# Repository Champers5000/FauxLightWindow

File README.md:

# FauxLightWindow
Designed to emulate the sun in a windowless space. 
* Uses GPS to determine your location and time in order to calculate luminosity at that location. 
* Electronics implement flickerless dimming of LEDs through a controllable constant current buck converter

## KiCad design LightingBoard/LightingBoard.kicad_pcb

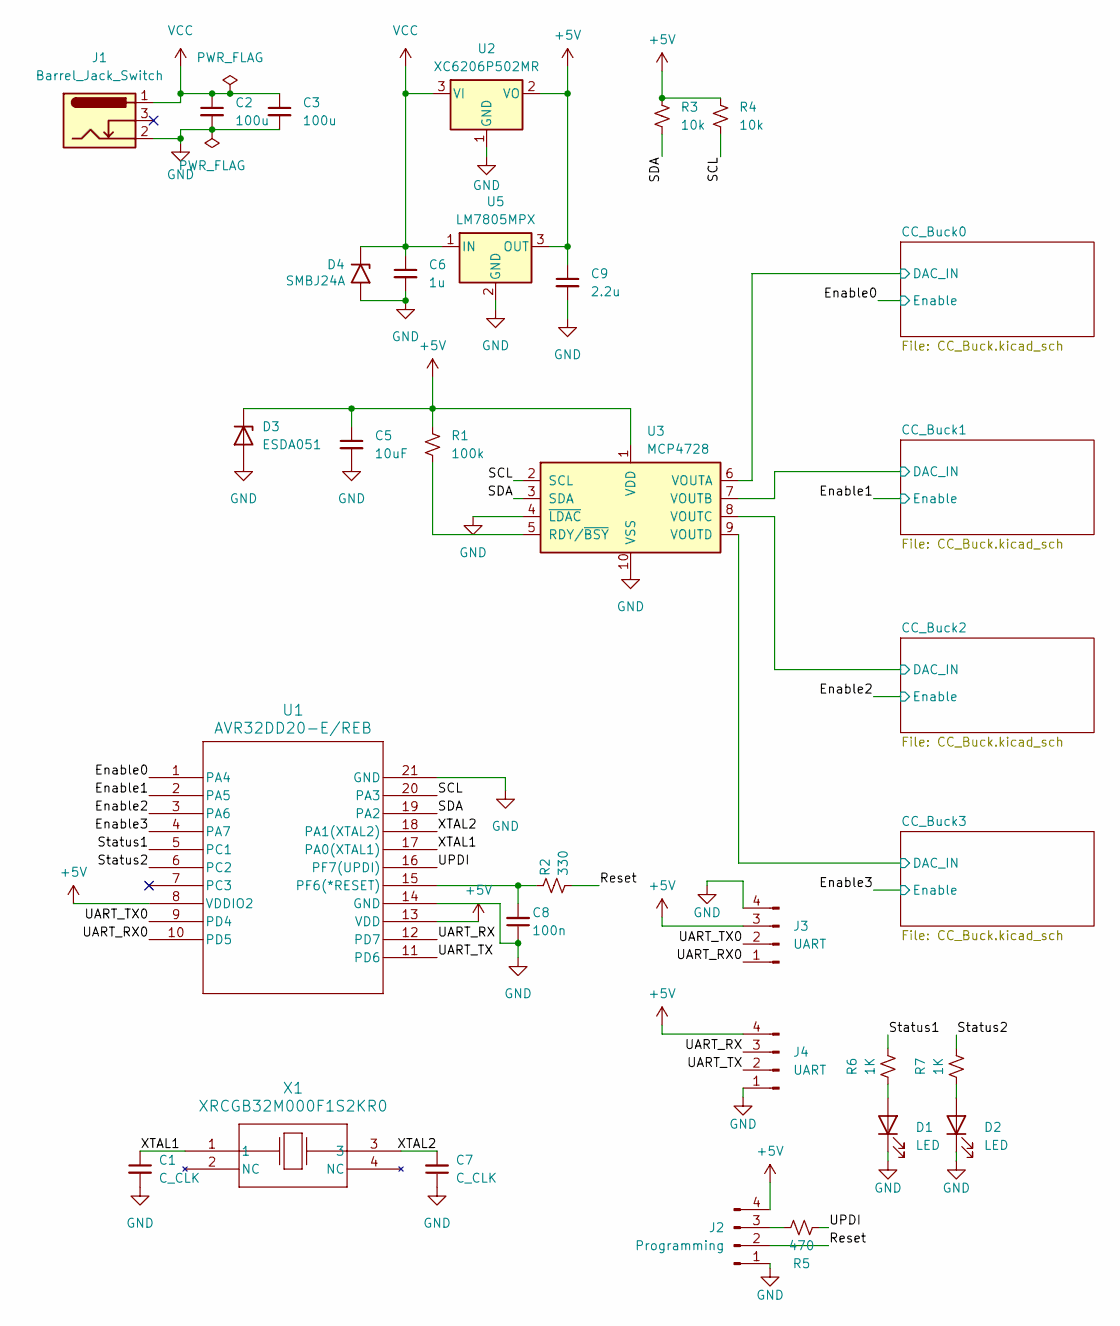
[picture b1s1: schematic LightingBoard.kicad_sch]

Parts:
C1, C7: C_CLK; C_0603_1608Metric
C2, C3: 100u; CP_Elec_6.3x7.7
C5: 10uF; C_0603_1608Metric
C6: 1u; C_0603_1608Metric
C8: 100n; C_0603_1608Metric
C9: 2.2u; C_0603_1608Metric
D1, D2: LED; LED_0805_2012Metric
D3: ESDA051; D_SOD-323
D4: SMBJ24A; D_SMB
J1: Barrel_Jack_Switch; BarrelJack_Horizontal
J2: Programming; PinSocket_1x04_P2.54mm_Vertical
J3: UART; JST_SH_BM04B-SRSS-TB_1x04-1MP_P1.00mm_Vertical
J4: UART; PinSocket_1x04_P2.54mm_Vertical
R1: 100k; R_0603_1608Metric
R2: 330; R_0603_1608Metric
R3, R4: 10k; R_0603_1608Metric
R5: 470; R_0603_1608Metric
R6, R7: 1K; R_0603_1608Metric
U1: AVR32DD20-E/REB; VQFN-20-1EP_3x3mm_P0.4mm_EP1.7x1.7mm
U2: XC6206P502MR; SOT-23
U3: MCP4728; MSOP-10_3x3mm_P0.5mm
U5: LM7805MPX; SOT-223-3_TabPin2
X1: XRCGB32M000F1S2KR0; Crystal_SMD_2016-4Pin_2.0x1.6mm

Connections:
+5V: C5.1, C9.1, D3.1 (K), J2.4, J3.3, J4.4, R1.1, R3.1, R4.1, U1.8 (VDDIO2), U1.13 (VDD), U2.2 (VO), U3.1 (VDD), U5.3 (OUT); also elsewhere on the board
/CC_Buck0/DAC_IN: U3.6 (VOUTA); also elsewhere on the board
/CC_Buck1/DAC_IN: U3.7 (VOUTB); also elsewhere on the board
/CC_Buck2/DAC_IN: U3.8 (VOUTC); also elsewhere on the board
/CC_Buck3/DAC_IN: U3.9 (VOUTD); also elsewhere on the board
/Enable0: U1.1 (PA4); also elsewhere on the board
/Enable1: U1.2 (PA5); also elsewhere on the board
/Enable2: U1.3 (PA6); also elsewhere on the board
/Enable3: U1.4 (PA7); also elsewhere on the board
/Reset: J2.2, R2.1
/SCL: R4.2, U1.20 (PA3), U3.2 (SCL)
/SDA: R3.2, U1.19 (PA2), U3.3 (SDA)
/Status1: R6.2, U1.5 (PC1)
/Status2: R7.2, U1.6 (PC2)
/UART_RX: J4.3, U1.12 (PD7)
/UART_RX0: J3.1, U1.10 (PD5)
/UART_TX: J4.2, U1.11 (PD6)
/UART_TX0: J3.2, U1.9 (PD4)
/UPDI: R5.1, U1.16 (PF7(UPDI))
/XTAL1: C1.1, U1.17 (PA0(XTAL1)), X1.1
/XTAL2: C7.2, U1.18 (PA1(XTAL2)), X1.3
GND: C1.2, C2.2, C3.2, C5.2, C6.2, C7.1, C8.1, C9.2, D1.1 (K), D2.1 (K), D3.2 (A), D4.2 (A2), J1.2, J2.1, J3.4, J4.1, U1.14 (GND), U1.21 (GND), U2.1 (GND), U3.4 (~LDAC), U3.10 (VSS), U5.2 (GND); also elsewhere on the board
unnamed: D1.2 (A), R6.1
unnamed: D2.2 (A), R7.1
unnamed: J2.3, R5.2
unnamed: C8.2, R2.2, U1.15 (PF6(*RESET))
unnamed: R1.2, U3.5 (RDY/~BSY)
VCC: C2.1, C3.1, C6.1, D4.1 (A1), J1.1, U2.3 (VI), U5.1 (IN); also elsewhere on the board

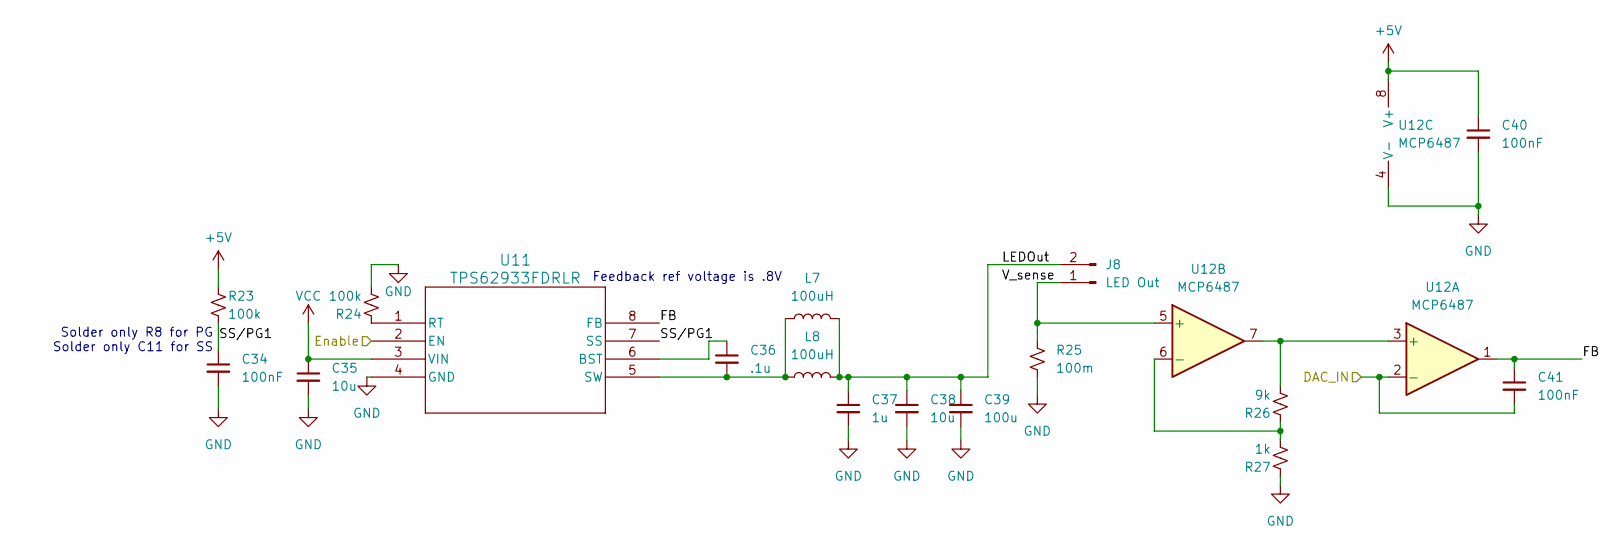
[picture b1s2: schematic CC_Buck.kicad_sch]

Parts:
C34, C40, C41: 100nF; C_0603_1608Metric
C35: 10u; C_0603_1608Metric
C36: .1u; C_0603_1608Metric
C37: 1u; C_0805_2012Metric
C38: 10u; C_0805_2012Metric
C39: 100u; CP_Elec_6.3x7.7
J8: LED Out; PinSocket_1x02_P2.54mm_Vertical
L7: 100uH; 7447231101
L8: 100uH; IND_BOURNS_SDR1307
R23, R24: 100k; R_0603_1608Metric
R25: 100m; R_1206_3216Metric
R26: 9k; R_0603_1608Metric
R27: 1k; R_0603_1608Metric
U11: TPS62933FDRLR; SOT-583-8
U12: MCP6487; MSOP-8_3x3mm_P0.65mm

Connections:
+5V: C40.1, R23.2, U12.8 (V+); also elsewhere on the board
/CC_Buck3/DAC_IN: C41.2, U12.2 (-); also elsewhere on the board
/CC_Buck3/FB: C41.1, U11.8 (FB), U12.1
/CC_Buck3/LEDOut: C37.1, C38.1, C39.1, J8.2, L7.2, L8.2
/CC_Buck3/SS/PG1: C34.1, R23.1, U11.7 (SS)
/CC_Buck3/V_sense: J8.1, R25.1, U12.5 (+)
/Enable3: U11.2 (EN); also elsewhere on the board
GND: C34.2, C35.2, C37.2, C38.2, C39.2, C40.2, R24.1, R25.2, R27.2, U11.4 (GND), U12.4 (V-); also elsewhere on the board
unnamed: C36.1, U11.6 (BST)
unnamed: R24.2, U11.1 (RT)
unnamed: C36.2, L7.1, L8.1, U11.5 (SW)
unnamed: R26.1, U12.3 (+), U12.7
unnamed: R26.2, R27.1, U12.6 (-)
VCC: C35.1, U11.3 (VIN); also elsewhere on the board

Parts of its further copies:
C10, C16, C17, C18, C24, C25, C26, C32, C33: 100nF; C_0603_1608Metric
C11, C19, C27: 10u; C_0603_1608Metric
C12, C20, C28: .1u; C_0603_1608Metric
C13, C21, C29: 1u; C_0805_2012Metric
C14, C22, C30: 10u; C_0805_2012Metric
C15, C23, C31: 100u; CP_Elec_6.3x7.7
J5, J6, J7: LED Out; PinSocket_1x02_P2.54mm_Vertical
L1, L3, L5: 100uH; 7447231101
L2, L4, L6: 100uH; IND_BOURNS_SDR1307
R8, R9, R13, R14, R18, R19: 100k; R_0603_1608Metric
R10, R15, R20: 100m; R_1206_3216Metric
R11, R16, R21: 9k; R_0603_1608Metric
R12, R17, R22: 1k; R_0603_1608Metric
U4, U7, U9: TPS62933FDRLR; SOT-583-8
U6, U8, U10: MCP6487; MSOP-8_3x3mm_P0.65mm

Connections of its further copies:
+5V: C17.1, C24.1, C32.1, R8.2, R13.2, R18.2, U6.8 (V+), U8.8 (V+), U10.8 (V+); also elsewhere on the board
/CC_Buck0/DAC_IN: C16.2, U6.2 (-); also elsewhere on the board
/CC_Buck0/FB: C16.1, U4.8 (FB), U6.1
/CC_Buck0/LEDOut: C13.1, C14.1, C15.1, J5.2, L1.2, L2.2
/CC_Buck0/SS/PG1: C10.1, R8.1, U4.7 (SS)
/CC_Buck0/V_sense: J5.1, R10.1, U6.5 (+)
/CC_Buck1/DAC_IN: C25.2, U8.2 (-); also elsewhere on the board
/CC_Buck1/FB: C25.1, U7.8 (FB), U8.1
/CC_Buck1/LEDOut: C21.1, C22.1, C23.1, J6.2, L3.2, L4.2
/CC_Buck1/SS/PG1: C18.1, R13.1, U7.7 (SS)
/CC_Buck1/V_sense: J6.1, R15.1, U8.5 (+)
/CC_Buck2/DAC_IN: C33.2, U10.2 (-); also elsewhere on the board
/CC_Buck2/FB: C33.1, U9.8 (FB), U10.1
/CC_Buck2/LEDOut: C29.1, C30.1, C31.1, J7.2, L5.2, L6.2
/CC_Buck2/SS/PG1: C26.1, R18.1, U9.7 (SS)
/CC_Buck2/V_sense: J7.1, R20.1, U10.5 (+)
/Enable0: U4.2 (EN); also elsewhere on the board
/Enable1: U7.2 (EN); also elsewhere on the board
/Enable2: U9.2 (EN); also elsewhere on the board
GND: C10.2, C11.2, C13.2, C14.2, C15.2, C17.2, C18.2, C19.2, C21.2, C22.2, C23.2, C24.2, C26.2, C27.2, C29.2, C30.2, C31.2, C32.2, R9.1, R10.2, R12.2, R14.1, R15.2, R17.2, R19.1, R20.2, R22.2, U4.4 (GND), U6.4 (V-), U7.4 (GND), U8.4 (V-), U9.4 (GND), U10.4 (V-); also elsewhere on the board
unnamed: C12.1, U4.6 (BST)
unnamed: R9.2, U4.1 (RT)
unnamed: C12.2, L1.1, L2.1, U4.5 (SW)
unnamed: R11.1, U6.3 (+), U6.7
unnamed: R11.2, R12.1, U6.6 (-)
unnamed: C20.1, U7.6 (BST)
unnamed: R14.2, U7.1 (RT)
unnamed: C20.2, L3.1, L4.1, U7.5 (SW)
unnamed: R16.1, U8.3 (+), U8.7
unnamed: R16.2, R17.1, U8.6 (-)
unnamed: C28.1, U9.6 (BST)
unnamed: R19.2, U9.1 (RT)
unnamed: C28.2, L5.1, L6.1, U9.5 (SW)
unnamed: R21.1, U10.3 (+), U10.7
unnamed: R21.2, R22.1, U10.6 (-)
VCC: C11.1, C19.1, C27.1, U4.3 (VIN), U7.3 (VIN), U9.3 (VIN); also elsewhere on the board

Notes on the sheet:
Feedback ref voltage is .8V
Solder only R8 for PG Solder only C11 for SS

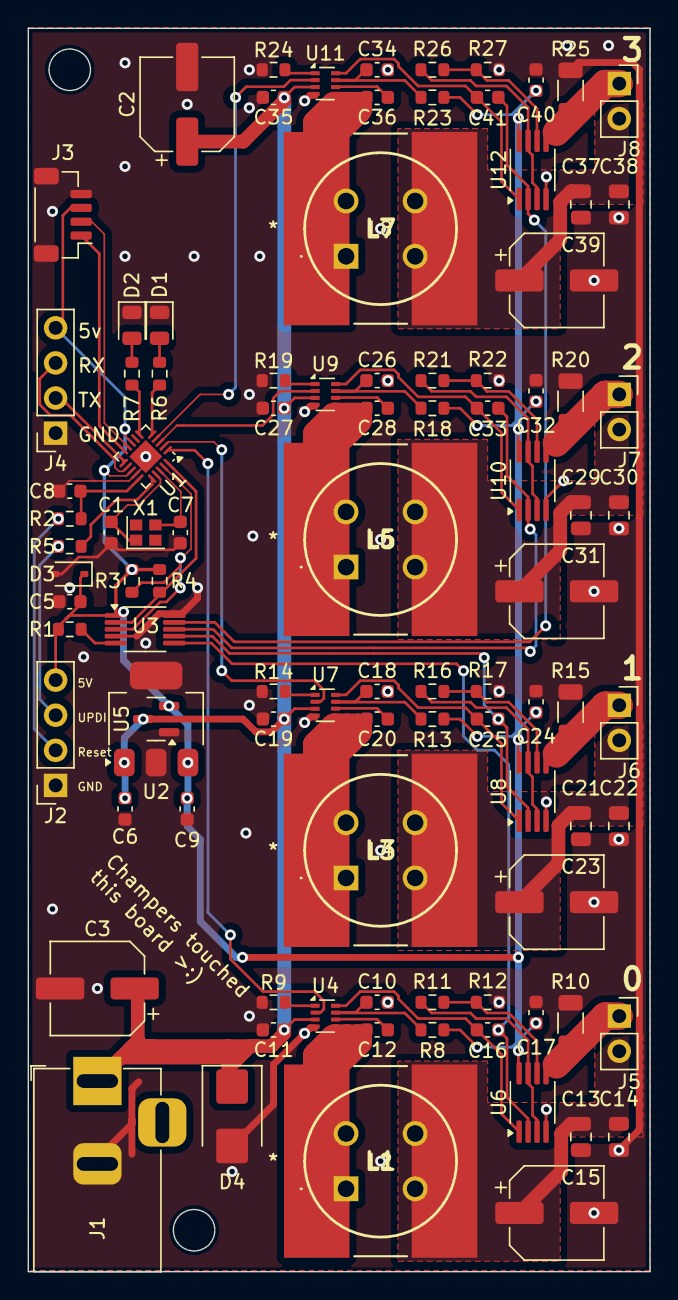
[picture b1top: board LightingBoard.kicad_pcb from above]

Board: 2 copper layers, 45.0 x 90.0 mm, 100 parts (0 on the bottom side), 64 nets.

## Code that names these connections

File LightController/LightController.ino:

#define F_CPU 24000000UL
#include <stdint.h>

#include <avr/io.h>
// #include <avr/interrupt.h>
// #include <util/delay.h>


// #include "inc/Drivers/StatusLED.h"
#include "inc/Application/FaultState.h"
#include "inc/Application/XYZ1931.h"
#include "inc/Application/SunDial.h"
#include "inc/Drivers/I2C_DAC.h"

#include <Wire.h>
#include <TinyGPSPlus.h>

#define NUM_ILLUMINANTS 3

TinyGPSPlus gps;
SunDial sd;
MCP4728 dac;
char buf[100];
float specDistFromSunDial(float wavelen) {
  return sd.atmosphericRadiator(wavelen);
}

void setLed(bool a, bool b) {
  digitalWrite(PIN_PC1, a);
  digitalWrite(PIN_PC2, b);
}


//very basic color calculator to run on HW for now
void setup() {

  // PORTA.DIRSET = 0xF0; // PA7 through PA4 represent channel 3-0 enable bits
  // PORTA.OUT = 0;

  //-------------------------INIT-------------------------------
  Serial.swap(3);
  Serial1.swap(2);

  Serial.begin(9600);
  Serial1.begin(115200);
  
  // DAC Init
  dac = MCP4728();
  // Finished DAC Init

  // status led init
  // PORTC.DIRSET = 0b0110;
  // PORTC.OUT = 0;
  pinMode(PIN_PC1, OUTPUT);
  pinMode(PIN_PC2, OUTPUT);
  pinMode(PIN_PA4, OUTPUT);
  pinMode(PIN_PA5, OUTPUT);
  pinMode(PIN_PA6, OUTPUT);
  delay(2000);
  digitalWrite(PIN_PA4, OUTPUT);
  digitalWrite(PIN_PA5, OUTPUT);
  digitalWrite(PIN_PA6, OUTPUT);

  //-------------------------END INIT-------------------------------

  // //code to write EEPROM to dac
  // dac.writeEEPROM(0);
  // while(true){
  //   digitalWrite(PIN_PC1, HIGH);
  //   delay(321);
  //   digitalWrite(PIN_PC1, LOW);
  //   delay(679);
  // }


  //code to take input uart and put it on all dac channels
  uint16_t allChannels[4] = {0x0F, 0x0F, 0x0F, 0x0F};
  while(true){
    setLed(1,0);
    if(Serial1.available()){
      allChannels[0] = Serial1.parseInt();
        if((allChannels[0] & 0xF000) == 0 && allChannels[0] != 0){
          Serial1.print("set output to ");
          Serial1.println(allChannels[0]);
        }else{
          Serial1.println("invalid input");
          allChannels[0] = allChannels[3];
        }
    }else{
      Serial1.println(allChannels[0]);
    }
    for(uint8_t i = 1; i<3; ++i){
      allChannels[i] = allChannels[0];
    }
    dac.setAllChannels(allChannels);
    setLed(0,1);
    delay(500);
  }

  // sd = SunDial();

  // float lon = 0;
  // float lat = 0;
  // uint32_t time = 0;

  // while (1) {
  //   smartdelay(10);
  //   if (gps.location.lat() == 0) {
  //     lat = 30.266666f;
  //     lon = -97.733330f;
  //   }

  //   time = time + 100;  //(uint32_t) (gps.time.hour())  * 3600ul + gps.time.minute()*60+gps.time.second();
  //   // Serial1.println(time);
  //   // Serial1.println(gps.time.second());

  //   if (time == 0) {
  //     continue;
  //   }
  //   if (time >= 86400UL) {
  //     time = 0;
  //   }

  //   // sd.update(sd.convertDateToDays(gps.date.day(), gps.date.month()) , gps.time.hour()*3600+gps.time.minute()*60+gps.time.second(),
  //   //           gps.location.lat(), gps.location.lng(), gps.altitude.meters());


  //   sd.update(
  //     sd.convertDateToDays(23, 8),
  //     time,
  //     lat,
  //     lon,
  //     150);

  //   XYZ1931 XYZtarget = XYZ1931::XYZFromSpecDistFunc(&specDistFromSunDial);
  //   float cct = XYZtarget.getCCT();
  //   float weights[4];
  //   xyY colorTarget = CCT_To_xyY(cct);
  //   xyY clippedT = clipSignal(colorTarget, 3);
  //   // Serial1.print(cct);
  //   // Serial1.print(" ");
  //   // Serial1.print(colorTarget.x);
  //   // Serial1.print(" ");
  //   // Serial1.print(colorTarget.y);
  //   // Serial1.print("    ");
  //   // Serial1.print(clippedT.x);
  //   // Serial1.print(" ");
  //   // Serial1.print(clippedT.y);
  //   // Serial1.println();



  //   calculateWeightsForClippedTarget(colorTarget, weights, NUM_ILLUMINANTS);
  //   sprintf(buf, "utcT=%lu, T=%lu, cct = %lu", time, sd.UTCtoSolarLocal(time,sd.day, sd.longitude)/3600, (uint32_t) cct);
  //   Serial1.println(buf);
  //   for(uint8_t j=0; j<NUM_ILLUMINANTS; ++j){
  //     weights[j] *= sd.intensity;
  //     Serial1.print(weights[j]);
  //     Serial1.print(" ");
  //   }
  //   Serial1.println();
  //   setLed(0,1);
  //   dac.setAllChannelBrightness(weights);
  // }
}

static void smartdelay(unsigned long ms) {
  unsigned long start = millis();
  do {
    while (Serial.available())
      gps.encode(Serial.read());
  } while (millis() - start < ms);
}

void loop() {
}






// SunDial s;
// XYZ1931 test;

// float specDistFromSunDial(float wavelen){
//     return s.atmosphericRadiator(wavelen);
// }

// int main()
// {
//     printf("wavelen,X,Y,Z\n");
//     s = SunDial();

//     for(int i=0; i<86400; i+=300){
//         uint32_t timehere = SunDial::UTCtoSolarLocal(i, 36, -97.733330);
//         int hour = timehere / 3600;
//         int minute = (timehere % 3600)/60;
//         int second = timehere %60;
//         s.update(216, i , 30.266666/180*M_PIf, -97.733330/180*M_PIf, 156);
//         printf("Austin's hour angle for %d:%d:%d is %f, intensity= %f\n", hour, minute, second, SunDial::hourAngle(i, 36, -97.733330), s.intensity);
//         test = XYZ1931(&specDistFromSunDial);
//         printf("airmass is %f, cct is %f\n", s.airMass, test.getCCT());
//     }
//     calculateTarget(myIlluminants[0]);
//     return 0;
// }

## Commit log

2023-11-04 init commit
2023-11-10 add gitignore
2023-11-14 Circuit and PCB
2024-01-04 add cost estimates
2024-01-04 NO MORR DINOSAURR
2024-01-07 fix some issues
2024-01-14 hello world
2024-01-14 better file structure
2024-01-15 HEHEHE
2024-02-06 ignore gerber
2024-02-06 working intensity code
2024-02-06 actually push the code
2024-02-06 seeing colors
2024-02-07 XYZee ur RGBee
2024-02-18 new design based on AVR32DD20
2024-03-30 update to kicad 8
2024-03-30 center a via
2024-07-14 save some code
2024-07-14 ignore backups
2024-07-14 MORE PINS
2024-07-16 test dxcore
2024-07-21 imma subsheet into your sheets
2024-07-24 almost theregit status!
2024-07-25 woooooo finally done
2024-07-25 who needs logging
2024-09-16 update board components
2024-12-17 outdated
2025-01-09 less components
2025-02-01 fabbed
2025-02-02 testing this stuff
2025-02-05 something?
